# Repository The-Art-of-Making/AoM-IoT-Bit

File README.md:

# AOM IoT Bit - Spring 2022
------------------------------------

## Summary
------------------------------------
The AOM IoT Bit, is a device that allows students to prototype with IoT, without the overhead of all the logistics that come with setup.

The goal is that students will be able to **easily link an AOM IoT Bit to a LittleBits circuit, and get that circuit to send and/or recieve data through a cloud-based system**.

**\*\*Insert Image Here\*\***

------------------------------------
## Usage of a fully setup AOM IoT Bit
------------------------------------
To Use the AOM IoT Bit, all a student needs to do is the following:

- Open up a serial connection and ... add their credentials to the arduino_secrets_mine.h file ***[DO NOT SHARE THIS!]***

- Push the code to the MKR 1010 Arduino Board.

- Plug it in to their LittleBits circuit, and set the onboard switch to the proper setting (Push, Poll, Both)

------------------------------------
## Building an AOM IoT Bit
------------------------------------
We have started by using the Arduino MKR 1010 Board, Found Here:
**\*\*Insert Build Instructions Here\*\***

------------------------------------
## Initial Setup of an AOM IoT Bit
------------------------------------
**\*\*Insert Setup Instructions Here\*\***

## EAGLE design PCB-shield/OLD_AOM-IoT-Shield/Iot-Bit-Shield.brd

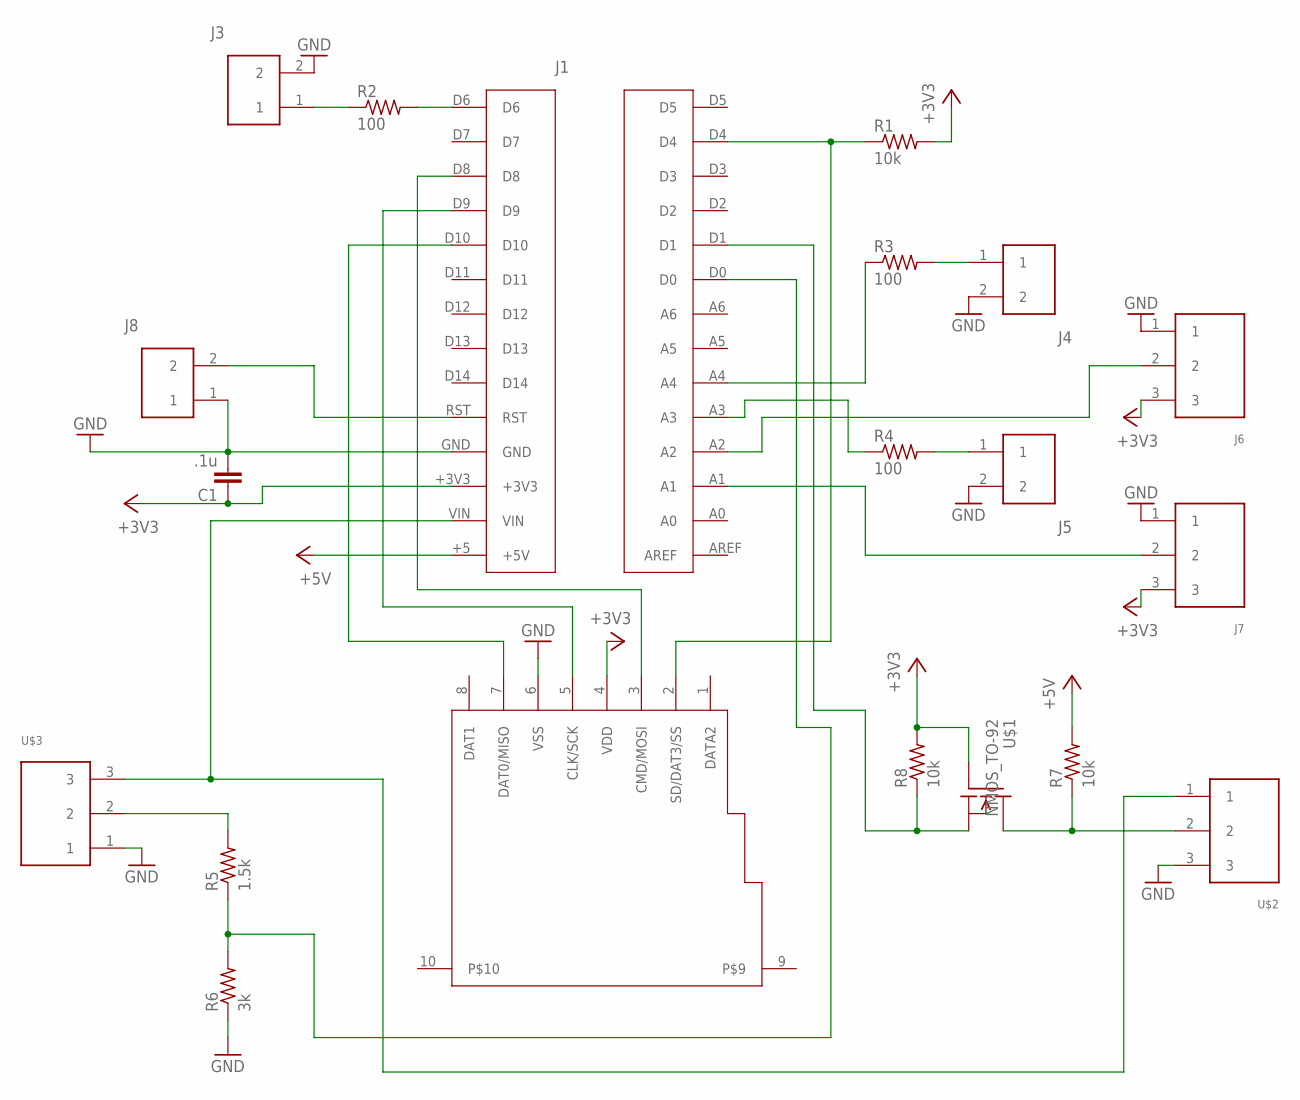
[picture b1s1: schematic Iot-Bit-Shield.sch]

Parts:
C1: .1u; C025-024X044
J1: MKR1010-HEADER-14POS; SIP-1X14
J2: 114-00841-68; AMPHENOL-SD-SMT
J3, J4, J5, J8: JST-PH-2POS-CONN-TH
J6, J7: JST-PH-3POS-CONN-TH
R1, R7, R8: 10k; RES-LARGE-PAD
R2, R3, R4: 100; RES-LARGE-PAD
R5: 1.5k; RES-LARGE-PAD
R6: 3k; 0204/5
U$1: NMOS_TO-92; TO-92
U$2, U$3: HEADER-2.54MM; 2.54MM-HEADER

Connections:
+3V3: C1.1, J1.+3V3, J2.4 (VDD), J6.3, J7.3, R1.2, R8.2, U$1.1 (G)
+5V: J1.+5 (+5V), R7.2
GND: C1.2, J1.GND, J2.6 (VSS), J3.2, J4.2, J5.2, J6.1, J7.1, J8.1, R6.1, U$2.3, U$3.1
unnamed: J1.D4, J2.2 (SD/DAT3/SS), R1.1
unnamed: J1.D8, J2.3 (CMD/MOSI)
unnamed: J1.D9, J2.5 (CLK/SCK)
unnamed: J1.D10, J2.7 (DAT0/MISO)
unnamed: J1.D6, R2.2
unnamed: J1.A4, R3.1
unnamed: J1.A3, R4.1
unnamed: J3.1, R2.1
unnamed: J4.1, R3.2
unnamed: J5.1, R4.2
unnamed: J1.A1, J7.2
unnamed: J1.A2, J6.2
unnamed: J1.RST, J8.2
unnamed: R7.1, U$1.2 (D), U$2.2
unnamed: J1.D0, R5.1, R6.2
unnamed: R5.2, U$3.2
unnamed: J1.VIN, U$2.1, U$3.3
unnamed: J1.D1, R8.1, U$1.3 (S)

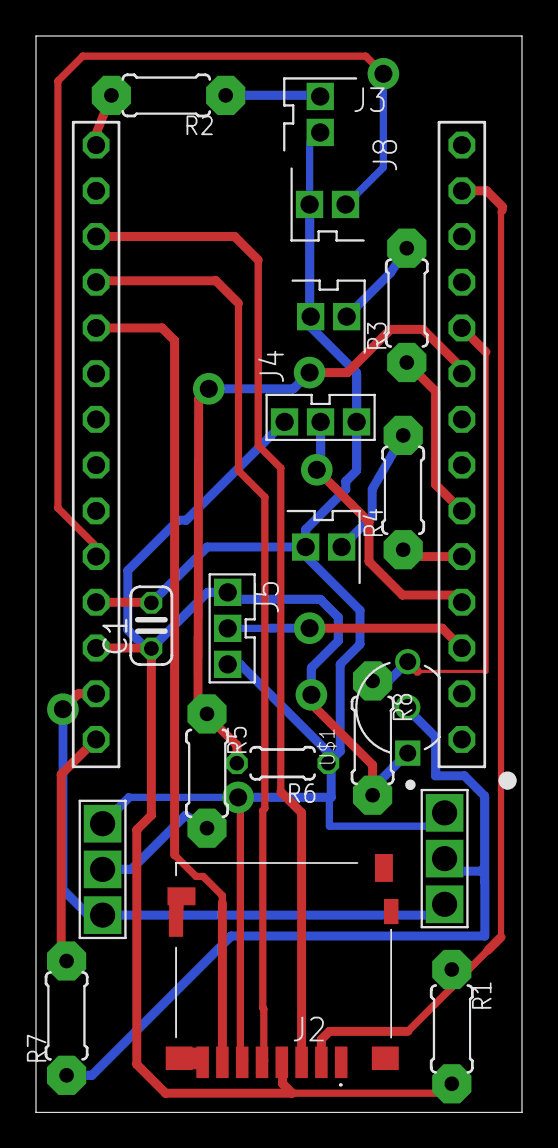
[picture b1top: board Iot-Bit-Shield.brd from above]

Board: 2 copper layers, 27.0 x 59.8 mm, 20 parts (0 on the bottom side), 21 nets.

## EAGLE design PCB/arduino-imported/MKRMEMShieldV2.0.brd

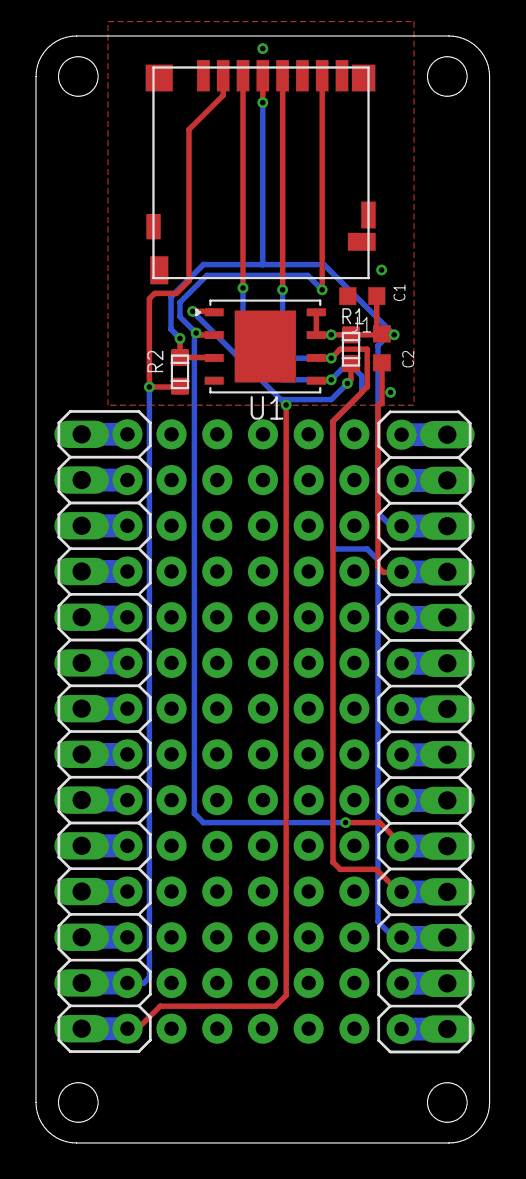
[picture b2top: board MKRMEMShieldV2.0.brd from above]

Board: 2 copper layers, 25.2 x 61.5 mm, 9 parts (0 on the bottom side), 8 nets.

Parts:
C1: 10u; 0603-1608X90N
C2: 100n; 0603-1608X90N
FRAME1: DNP; FRAME
J1: -; AMPHENOL_114-00841-68
JP1, JP4: -; 1X14-DOUBLE
R1, R2: 10k; C0603
U1: W25Q16; SON9P127_500X600X80L60X41T340X400N

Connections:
+3V3: C1.2, C2.1, J1.4, JP4.12, JP4.26, R1.2, R2.1, U1.3, U1.7, U1.8
+5V: JP4.14, JP4.28
GND: C1.1, C2.2, J1.6, J1.SH1, J1.SH2, J1.SH3, J1.SH4, JP4.11, JP4.25, U1.4, U1.9
unnamed: JP1.14, JP1.28, R1.1, U1.1
unnamed: J1.3, JP4.3, JP4.17, U1.5
unnamed: J1.5, JP4.4, JP4.18, U1.6
unnamed: J1.7, JP4.5, JP4.19, U1.2
unnamed: J1.2, JP1.13, JP1.27, R2.2

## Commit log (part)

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2022-01-15 Updated .h documentation, linked Google Doc
2022-01-16 added documentation to secrets, system diagram example
2022-01-16 Update IoT-Bit-Push.ino
    Allowed for 2 second interval. Swtiched to testing 1.0
2022-01-17 Added fixed .h, Pull changes
2022-01-19 Successfully Updated Push Code
    Tested and working.
    put foundation for easy integration with pull code.
2022-01-20 IOT BIT PROTOTYPE 1!!!!!
    With the turn of a potentiometer you can decide how frequently to Post/Poll data 🤩🤩🤩
    With the flick of 2!! Switches you can decide if you want to Post/Poll/Both/or Idle! ✨✨✨
    Wiring diagram will be uploaded soon!
2022-01-20 Update for hardware
    seems like mark removed the while(!Serial) for a reason haha.
2022-01-20 Reorganized File System
2022-01-20 Diagram of V1.0 Done!
2022-01-21 Created V1.1
    V1.1 was tested thoroughly, and incorporates many new features, with littleBits interfacing in mind.
    - Three signal lights now:
    - Blue indicates connectivity
    - Red_1 indicates upload attempt
    - Red_2 indicates download attempt
    - The Request Interval can be adjusted at any point
2022-01-22 reorganized Pinout to match protobit
2022-01-24 Most up to date pins with board v1.1
2022-01-25 Plz help mark
2022-01-25 Added files, fixed bugs. SD reads strings in to ASCII.
2022-01-26 Cannot split: failed to parse pass
2022-01-26 Try this?
2022-01-26 Fixes to SD failure lights
2022-01-27 Update Wifi_Setup.h
    Still Debugging
2022-01-27 Cleaned Up Debugging Code
2022-01-27 Pulled From SD Card Code
    Changes Now Allow SD Card Access Fully.
2022-01-27 Added Debugging Folder For Sketches
2022-01-28 Updated Pins For Hardware Design
    Leaving PWM Pins open for another day.
    Board orientation will be right side (out pin) is at the SD card, and the Top is where all the analog pins are.
    Also removed potentiometer from design to allow students to input this value in the file.
    Updated SD card protocol to:
    /* Format: REQUEST_RATE_SEC;SECRET_SSID;SECRET_PASS;SERVER_NAME;IO_USERNAME;IO_GROUP;IO_FEED_KEY;IO_KEY */
    /* Example: 2;Issam's iPhone;Pass123;io.adafruit.com;AOMUser1;AOMGroupA;AOMGroupAFeed1;AoMIoKeYsEcReT123 */
2022-01-28 Made pin changes
2022-01-28 Added housing v1
2022-01-29 Made SD Protocol More Robust
    SD protocol waits 5 seconds for you to put SD card in after three flashes.
    All lights flash for a second once SD card is read.
    No more Server definition required in secrets.txt
2022-01-29 Added new .gcode
2022-01-31 Added MKR Stl
2022-01-31 Student Helped Us 😜
2022-02-02 Deleted spurious files
2022-02-04 Added housing v3
2022-02-05 Added fixed base plate
2022-02-13 Adjusting Pins
2022-02-16 Added mem shield datasheet
2022-02-16 Moved files
2022-02-16 Updated fritzing schematic
2022-02-18 Confused
2022-03-06 Added updated CAD and media
2022-03-09 Added more supplementary CAD
2022-03-12 Added more media. New button .STEP file.
2022-04-26 Added final prototype picture
2022-07-17 Clean up old version-controlled revisions
2022-07-17 Revised fritzing schematic to 3.0
2022-07-17 New firmware rev
2022-07-17 Fix fritzing drawing
2022-07-17 Fix fritzing schematic 2
2022-07-30 Add code flowchart, add MOSFET to diagram, add post ISR
2022-07-31 Change swt/LED pinouts to accept interrupts, add ISRs to code
2022-07-31 Attach switch/LED interrupts
2022-07-31 Refactor main loop code, add blink LED function
2022-09-02 BOM digikey
2022-09-04 Breadboard update
2022-09-04 Interrupts for LEDs do not work'
2022-09-05 Cannot connect to Adafruit. Also ISRs are wonky
2022-09-05 Remove the LED ISRs, adjust blink function
2022-09-05 blink LED function not working???
2022-09-05 Thing work well
2022-09-07 Change to bi-directional logic level shifter - works.
2022-09-09 Add REV B of PCB. Don't want to lose.
2022-09-10 Move guide to drive. provide secrets template.
2022-09-12 For wiring pruposes, changed get status LED to A6, swapped post and get data pins
2022-09-12 Update breadboard to refelect pivot to SD shield
2022-09-14 Add peripheral test sketch
2022-09-14 Add LB power testing code to test directory
2022-09-15 The output pin for post switch depends on machine :(
2022-09-15 add secrets header file for creds if SD card not working
2022-09-15 media
2022-09-21 Split SD firmware and SD firmware into two separate directories
2022-10-14 ignore log files
2022-10-14 ignore __pycache__
2022-10-14 add requirements.txt
2022-10-14 database handler
2022-10-24 Add media
2022-10-29 Add most up-to-date CAD model rendering
2022-10-29 Add exploded view images & video
2022-11-01 Move BOMs to folder
2022-11-15 switch server handler to multithreading, add mqtt client
2022-12-20 mqtt docker container w/ password server
2022-12-23 nginx mqtt reverse proxy with upstream mqtt server lookup endpoint
2022-12-23 kubernetes handler
2022-12-24 remove SocketHandler, refactor Controller and ServerHandler to work with Flask
2022-12-24 controller kubernetes deployment
2022-12-24 mqtt reverse proxy kubernetes deployment
2022-12-24 ignore test scripts
2022-12-24 rename mqtt server deployment container
2022-12-24 mqtt reverse proxy env vars
2022-12-25 move mqtt server cert generation to runtime
2022-12-25 add pod command to kubernetes handler
2022-12-25 ignore certificate files
2022-12-25 kubernetes handler get pod count, check if pod is ready, check namespaces
2022-12-25 stop controller/shutdown servers on SIGINT/TERM
2022-12-25 remove users after sever created or shutdown, shutdown and remove all servers on stop
2022-12-26 remove mqtt-deployment simlink
2022-12-26 remove mqtt-deployment.yaml
2022-12-26 re-add mqtt server deployment file symlink
2022-12-27 temp fix to avoid async ngx.fetch() in parser
2022-12-27 also return server location in header in response from mqtt server lookup
2022-12-31 add build script for mqtt server
2023-01-01 run mqtt password server as cron job
2023-01-05 reverse proxy and lookup build scripts
2023-01-05 working reverse proxy parser.js
2023-01-05 load lookup ip into parser workaround
2023-01-06 add redis cache for mqtt server status
2023-01-09 Add media, migrate PCB work from Altium to Eagle. Creating new branch for PCB work
2023-01-09 add and delete clients and corresponding client devices
2023-01-09 nginx auth client validation
2023-01-09 reverse proxy auth with username and password
2023-01-09 Add Altium stuff to .gitignore
2023-01-09 Add all .intlib except for JST connectors
2023-01-09 rabbitmq mqtt server with http auth backend
2023-01-10 finish schematic capture of PCB. fritzing is all screwed up - refer to altium schematic
2023-01-10 refactor mqtt-controller to work with new db schemas and rabbitmq
2023-01-12 Finish PCB routing.
2023-01-14 Finish PCB, ordered. Also update CAD models
2023-01-14 add AoM-IoT-Bit-SD-Config submodule
2023-01-15 remove mongoose version keys
2023-01-15 ignore kubernetes mongouri secret
2023-01-15 fix controller mqtt servers startup and shutdown bugs
2023-01-15 MQTT servers query auth service via DNS
2023-01-17 submodule nanopb
2023-01-17 protobufs
2023-01-20 V3.1: Decrease SD card read delay. Automatically connect to WiFi regardless of switch state. Remove blinkLED function and replace with digitalWrites for now.
2023-01-20 Add SD card reading and WiFi connection test to text bench v1.0
2023-01-20 Fixed error skipping over SD card.
2023-01-22 fix delay when calling message_GET()
2023-01-23 Fix GET/POST issue with appending the group name before feed key.
2023-01-23 Update to v3.2 - ready for release. Reorganize files.
2023-01-24 Fix text bench. v1.0 --> v1.1
2023-02-03 Add updated Guide, picture. Begin REV3 BOM
2023-02-05 update ControllerMessage proto Type and ServerInfo
2023-02-05 rename protobuf compile script
2023-02-05 update mqtt-server http auth backend endpt
2023-02-05 add separate auth endpts for rabbitmq and mqtt servers
2023-02-07 threaded handlers for consuming and publishing messages to rabbitmq
2023-02-14 create and copy to mqtt-controller/application/protobufs when compiling protos
2023-02-14 mqtt-controller redesign
2023-02-16 basic structure of client actions service
2023-02-19 add and delete actions to and from db
2023-02-19 add actions to device config message published by mqtt-client-actions
2023-02-21 fix authenticating controllers to mqtt server
2023-02-21 remove excess logging from rabbitmq_handler
2023-02-21 fix publishing device configs with no actions
2023-02-21 database handler hashes password when adding controller
2023-02-21 mqtt-controller publishes device configs to mqtt servers
2023-02-22 retain config messages
2023-02-25 Add completed REV3 BOM
2023-02-25 Add .csv file for GH viewing
2023-03-04 add auth template to frontend
2023-03-04 frontend dev env
2023-03-04 Get rid of old v3.0 code for no SD card
2023-03-04 Reorganize code into backend, frontend, SD GUI, and Arduino firmware directories
2023-03-06 frontend icons and templating
2023-03-08 server, clients, and devices page layouts
2023-03-08 fix header history on non-auth pages
2023-03-08 update icons
2023-03-08 input range styling
2023-03-08 update client names
2023-03-09 update devices
2023-03-09 hide device controls for input devices
2023-03-09 add and delete actions
2023-03-10 enable cors on mqtt controller
2023-03-10 ignore frontend react builds
2023-03-10 authenticate web users as clients to mqtt servers
2023-03-10 replace urls with imported endpts and add config downloader for new clients
2023-03-15 add support for websocket connections to mqtt servers
2023-03-19 send commands to MQTT devices
2023-03-20 apply permissions for mqtt-controller to interact with kubernetes
2023-03-20 add navigation to account page
2023-03-20 current load balancer deployment endpoints
2023-03-20 add wifi creds to new client
2023-03-20 MicroSD_IO.h formatting
2023-03-25 basic setup for connecting to a MQTT server
2023-03-26 command digital output (device 1)
2023-03-29 add toast notifications
2023-06-10 ThreadHandler comments
2023-06-10 add heartbeat
2023-06-11 add updated and new services
2023-06-11 update frontend endpoint requests
2023-06-13 frontend topic builder
2023-06-14 refactor mqtt auth
2023-06-18 mqtt-config pub/sub client
2023-06-19 mqtt-config add mqtt client and option for messaged received callback and publishing to rabbitmq client
2023-06-20 include user uuid in mqtt client config file
2023-06-20 add status to device and client cards
2023-06-20 Devices page connects directly to mqtt server
2023-06-20 fix web-user-auth packages
2023-06-20 env values in mqtt config deployment must be strings
2023-06-20 convert select TODOs to Github issues
2023-06-20 create project with idf for esp32 firmware
2023-06-20 add protobufs component to idf project
2023-06-21 esp32 wifi test
2023-07-03 TopicBuilder module
2023-07-20 fix mqtt config deployment dependencies
2023-08-07 fix compiling esp32 firmware with protobufs
2023-08-21 submodule cml
2023-08-27 test mqtt-config main
2023-08-27 remove protobufs/nanopb submodule
2023-08-28 Create REV 4 PCB file
2023-08-28 Add ESP32 to library and schematic
2023-08-28 Add 3.3V regulator. Needs decoupling caps.
2023-08-29 SD card reader on there
2023-08-30 send commands to MQTT devices with protobufs
2023-08-30 temporary work around to update device control states
2023-08-30 Add LEDs'
2023-08-30 Add BOM doc. Not yet sure how we will fit this on a tiny board and do it on 2L.
2023-08-31 update device state and status
2023-09-01 Add TP and green LED to VCC
2023-09-01 Moving to multi-channel design for 7-segment displays
2023-09-01 Committing to rename file. Partway through transition to multi-sheet.
2023-09-01 New branch - old multi-channel hierarchy was not working.
2023-09-01 New sheet hierarchy with separate digit schematics. Shame.
2023-09-01 Board is mostly laid out. Will need to add a USB, FTDI, route, and add silkscreen.
2023-09-01 add will for device to mqtt-config main test
2023-09-02 start outlining new protobuf usage
2023-09-02 cml prefix client and device file names
2023-09-02 USB appears routed.
2023-09-03 create cml handler component
2023-09-03 All is placed and some is routed. 7-seg pinout may have to change.
2023-09-06 Route LEDs - pinout has changed
2023-09-11 Saving state
2023-09-11 Add images of example circuits:
2023-10-03 fix topic builder append

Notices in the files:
PCB/arduino-imported/MKRMEMShieldV2.0.brd:
Copyright (c) 2016-2017 Arduino LLC.  All right reserved. EAGLE Design Rules
parts and their libraries:
Arduino-ICs: Copyright (c) 2016-2017 Arduino LLC.  All right reserved.
Arduino-utility: This file is licensed under : CC-SA-BY-NC
